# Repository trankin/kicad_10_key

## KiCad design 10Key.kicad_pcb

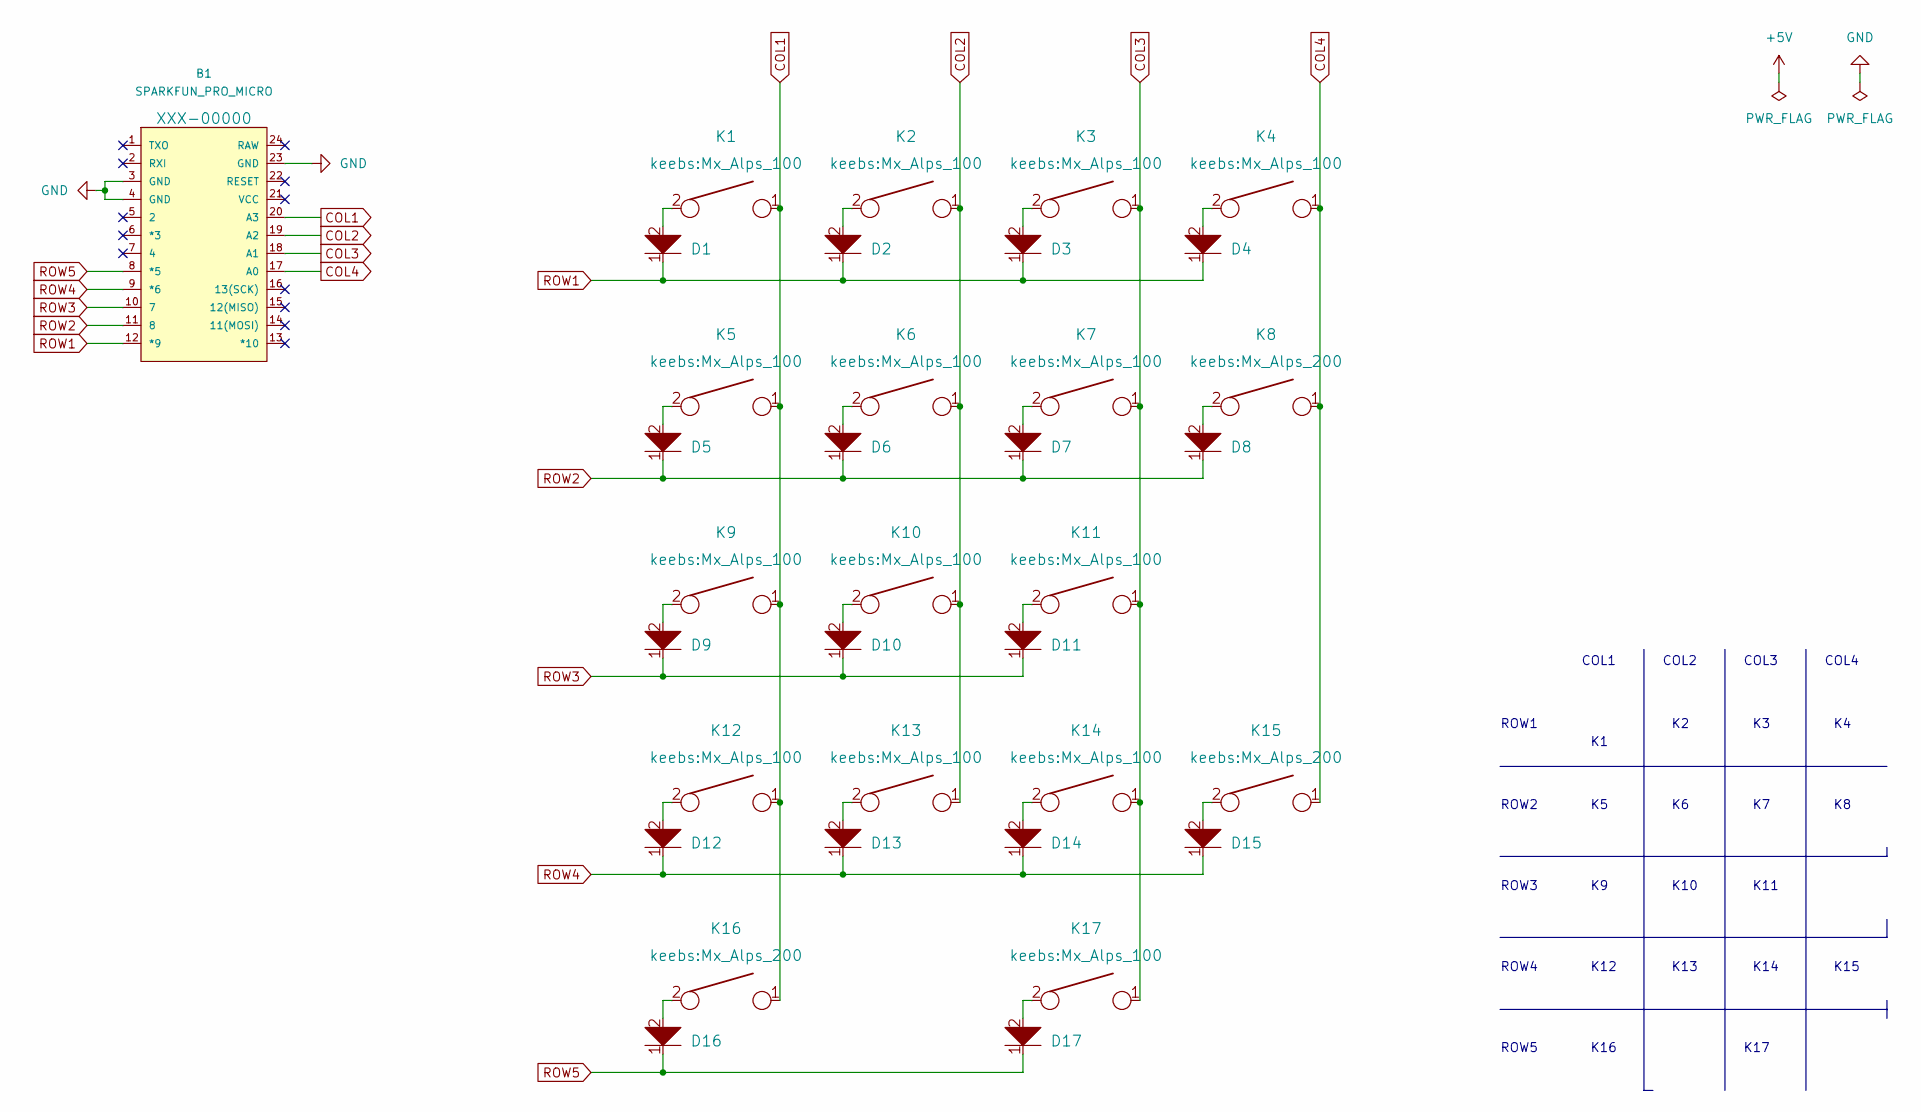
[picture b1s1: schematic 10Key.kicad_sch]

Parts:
B1: SPARKFUN_PRO_MICRO
D1, D2, D3, D4, D5, D6, D7, D8, D9, D10, D11, D12, D13, D14, D15, D16, D17: D; D_SOD123
K1, K2, K3, K4, K5, K6, K7, K9, K10, K11, K12, K13, K14, K17: KEYSW; Mx_Alps_100
K8, K15, K16: KEYSW; Mx_Alps_200

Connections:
COL1: B1.20 (A3), K1.1, K5.1, K9.1, K12.1, K16.1
COL2: B1.19 (A2), K2.1, K6.1, K10.1, K13.1
COL3: B1.18 (A1), K3.1, K7.1, K11.1, K14.1, K17.1
COL4: B1.17 (A0), K4.1, K8.1, K15.1
GND: B1.3 (GND), B1.4 (GND), B1.23 (GND)
unnamed: D1.2, K1.2
unnamed: D2.2, K2.2
unnamed: D3.2, K3.2
unnamed: D4.2, K4.2
unnamed: D5.2, K5.2
unnamed: D6.2, K6.2
unnamed: D7.2, K7.2
unnamed: D8.2, K8.2
unnamed: D9.2, K9.2
unnamed: D10.2, K10.2
unnamed: D11.2, K11.2
unnamed: D12.2, K12.2
unnamed: D13.2, K13.2
unnamed: D14.2, K14.2
unnamed: D15.2, K15.2
unnamed: D16.2, K16.2
unnamed: D17.2, K17.2
ROW1: B1.12 (*9), D1.1, D2.1, D3.1, D4.1
ROW2: B1.11 (8), D5.1, D6.1, D7.1, D8.1
ROW3: B1.10 (7), D9.1, D10.1, D11.1
ROW4: B1.9 (*6), D12.1, D13.1, D14.1, D15.1
ROW5: B1.8 (*5), D16.1, D17.1

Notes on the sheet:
ROW1
ROW2
ROW3
ROW4
ROW5
COL1
K12
K16
COL2
K10
K13
COL3
K17
K11
K14
COL4
K15

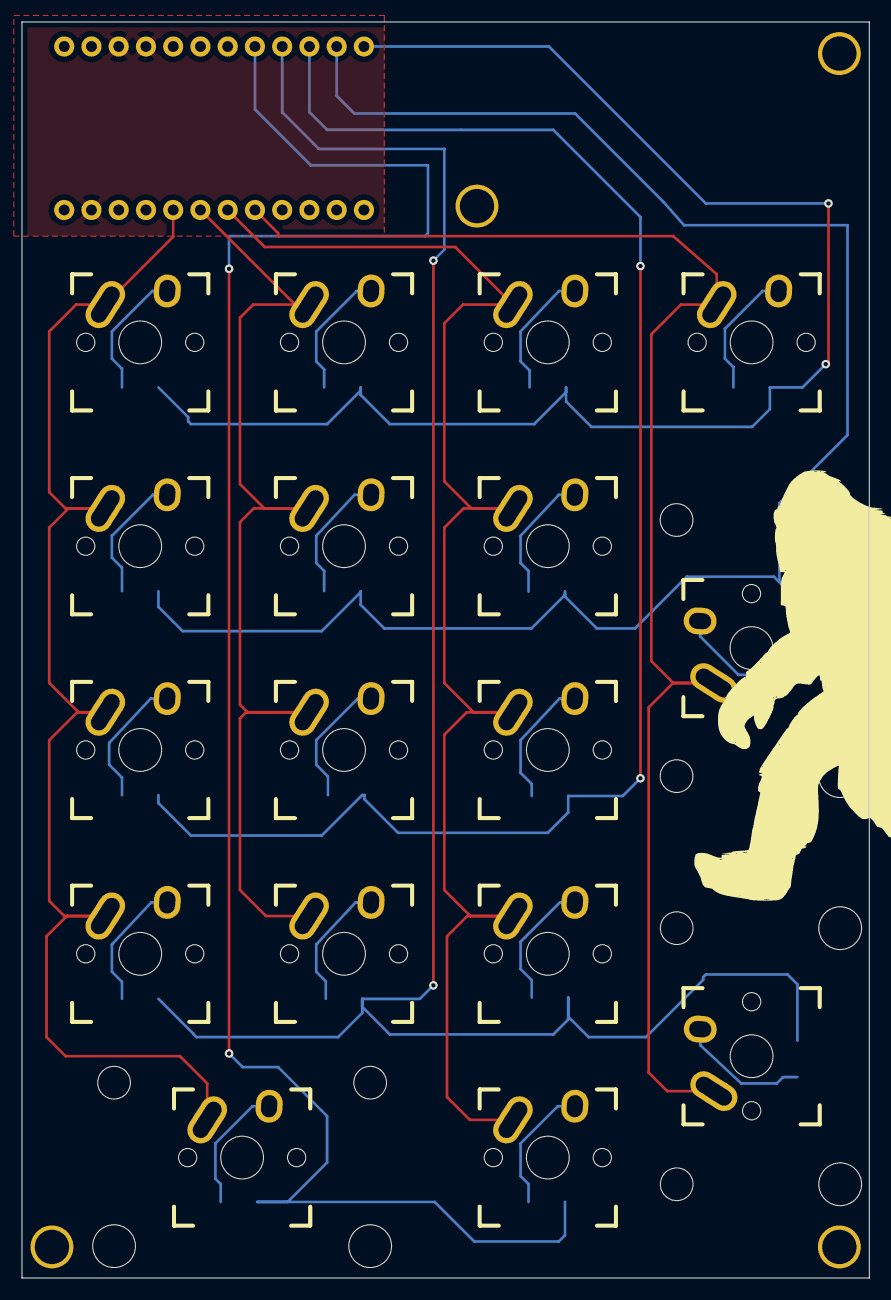
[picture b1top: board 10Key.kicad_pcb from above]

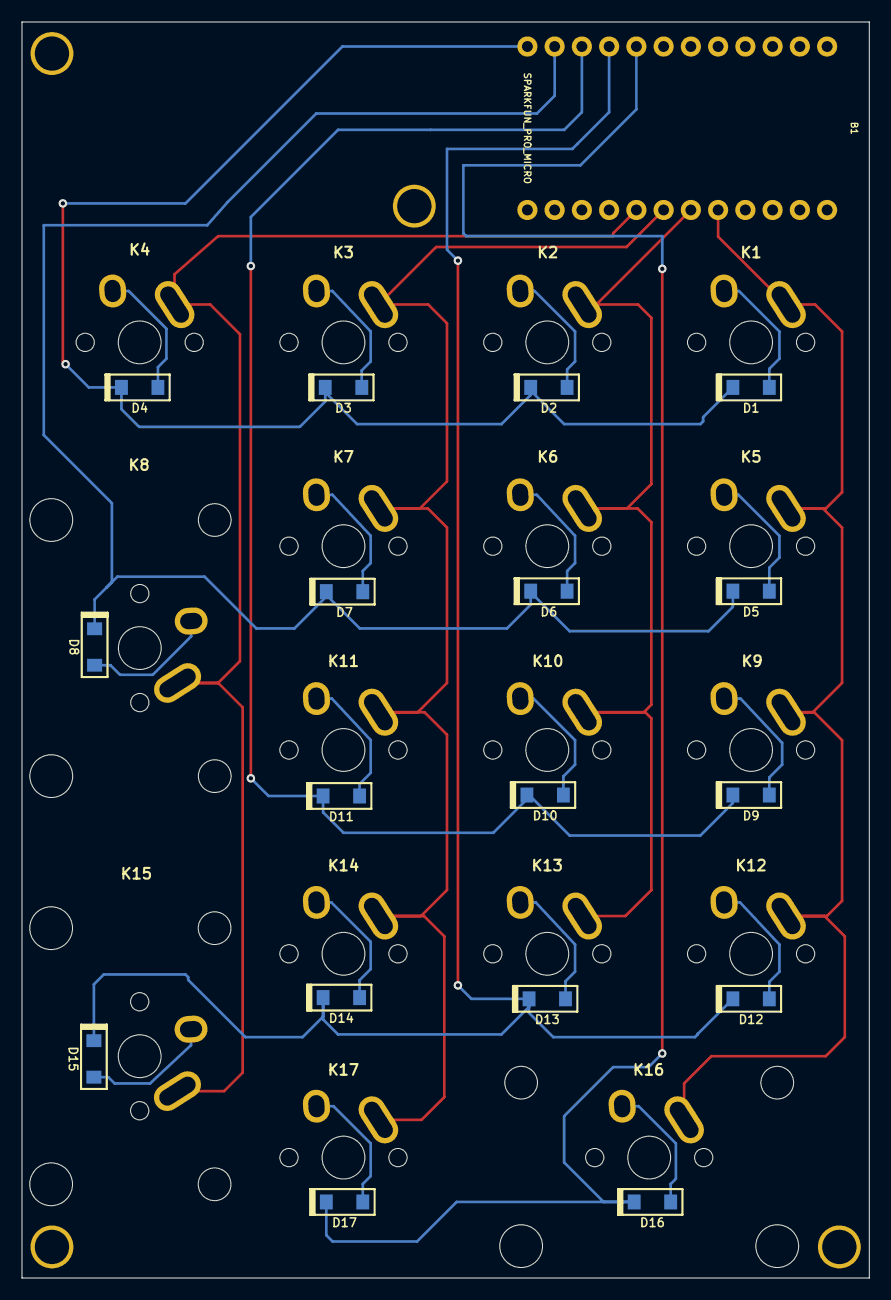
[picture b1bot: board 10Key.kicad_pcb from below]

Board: 2 copper layers, 79.0 x 117.1 mm, 39 parts (18 on the bottom side), 27 nets.

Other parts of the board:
HOLE_M3, HOLE_M3#2, HOLE_M3#3, HOLE_M3#4: VAL**; HOLE_M3
